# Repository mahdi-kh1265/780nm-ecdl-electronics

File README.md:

# 780nm-ecdl-electronics

Control, interface, piezo-actuation, and power electronics for POSM's 780 nm Littrow external-cavity diode laser.

This repository contains the custom electronics surrounding POSM's 780 nm ECDL used for rubidium spectroscopy, modulation-transfer spectroscopy (MTS), and laser-frequency stabilization.

The system is divided into three hardware projects:

1. **`ecdl-laser-bboard`** — laser/TEC controller interface, slow current bias, fast current modulation, monitoring, and Red Pitaya/FPGA connectivity.
2. **`780nm-ecdl-grating`** — high-voltage piezoelectric grating actuator driver for ECDL tuning, scanning, and slow lock correction.
3. **`780nm-grating-psu`** — dedicated low-voltage and high-voltage power supply for the grating driver. **Currently in development.**

---

# ECDL Hardware Context

The current system is designed around a 780 nm Littrow ECDL for the rubidium D2 region.

The broader laser assembly includes:

* 780 nm laser diode
* temperature-controlled TO-can mount
* diffraction grating in Littrow configuration
* piezoelectric grating actuator
* optical isolator
* free-space output optics
* fiber launch into the spectroscopy system
* MTS-based atomic frequency reference

The electronics in this repository do **not** contain the complete spectroscopy lock. MTS RF/demodulation electronics and FPGA lock logic are maintained separately.

---

# 1. `ecdl-laser-bboard`

## Laser / TEC Interface and Current-Control Baseboard

`ecdl-laser-bboard` is the central electrical interface between the laser assembly, commercial laser/TEC controller, Red Pitaya/FPGA control system, and monitoring hardware.

It is intentionally an **interface and control-conditioning board**, not a replacement precision laser-current driver.

The commercial LD/TEC controller remains responsible for the actual regulated laser current and TEC control.

# 2. `780nm-ecdl-grating`

## High-Voltage ECDL Grating / PZT Driver

The second major PCB drives the piezoelectric actuator mounted behind the Littrow grating.

Moving the piezo changes the diffraction-grating angle and external-cavity length, which changes the ECDL frequency.

The board is intended for:

* laser-frequency scanning
* finding rubidium spectroscopy features
* setting the PZT operating point
* lock acquisition
* slow frequency correction
* recentering the fast current actuator during long locks

---

# 3. `780nm-grating-psu`

## Dedicated Grating-Driver Power Supply

> **Current repository status: this PCB is still in development.**

The intended role of this board is to generate all rails required by `780nm-ecdl-grating` from a low-voltage system input.

Primary design goals include:

* low-noise analog rails
* controlled startup
* current limiting and fault protection
* sufficient +155 V power for dynamic piezo charging
* proper high-voltage spacing
* low coupling from the switching converters into the analog control circuitry

The committed KiCad project should be treated as a placeholder until the PSU design is frozen and reviewed.

# 4. Repository Structure

```text
780nm-ecdl-electronics/
│
├── ecdl-laser-bboard/
│   ├── ecdl-laser-bboard.kicad_sch
│   ├── sch2.kicad_sch
│   ├── sch3.kicad_sch
│   ├── ecdl-laser-bboard.kicad_pcb
│   ├── ecdl-laser-bboard.kicad_pro
│   └── libraries/
│
├── 780nm-ecdl-grating/
│   ├── 780nm-ecdl-grating.kicad_sch
│   ├── 780nm-ecdl-grating.kicad_pcb
│   ├── 780nm-ecdl-grating.kicad_pro
│   └── libraries/
│
├── 780nm-grating-psu/
│   ├── 780nm-grating-psu.kicad_sch
│   ├── 780nm-grating-psu.kicad_pcb
│   └── 780nm-grating-psu.kicad_pro
│
├── LICENSE
└── README.md
```

The current projects use **KiCad 10** format.

---

# 5. Major Components

| Function                      | Component                      | PCB                  |
| ----------------------------- | ------------------------------ | -------------------- |
| High-voltage PZT amplifier    | TI OPA462                      | `780nm-ecdl-grating` |
| Precision analog buffering    | TI OPA192                      | `780nm-ecdl-grating` |
| Precision reference           | ADR4550                        | `780nm-ecdl-grating` |
| Slow laser-current bias DAC   | TI DAC80501                    | `ecdl-laser-bboard`  |
| Precision analog conditioning | TI OPA4192                     | `ecdl-laser-bboard`  |
| True-zero negative supply     | TI LM7705                      | `ecdl-laser-bboard`  |
| Input protection / eFuse      | TPS25947 family                | `ecdl-laser-bboard`  |
| Low-noise power conversion    | LT862x family                  | `ecdl-laser-bboard`  |
| ECDL mount interface          | DB9 / DB15                     | `ecdl-laser-bboard`  |
| FPGA/control interface        | Red Pitaya header / analog I/O | `ecdl-laser-bboard`  |

Refer to the KiCad schematics rather than this table for current component values and installed options.

---

# 6. Recommended Bring-Up Sequence

The complete ECDL should **not** be the first load connected during PCB bring-up.

Each board should be tested independently first.

## `ecdl-laser-bboard`

1. Inspect for assembly faults and shorts.
2. Verify resistance from each power rail to ground.
3. Apply current-limited 12 V with the laser and TEC disconnected.
4. Verify eFuse behavior.
5. Verify all 5 V and logic rails.
6. Verify the LM7705 negative rail.
7. Verify DAC80501 communication over SPI.
8. Sweep the slow-bias DAC and measure `V_BIAS`.
9. Apply a known voltage to `RP_IN`.
10. Verify each fast-loop sensitivity setting.
11. Verify the complete summed `EXT_LD_SET` transfer function.
12. Verify `RP_EN` / `LD_SHD` behavior.
13. Inject known monitor voltages and verify each buffer.
14. Verify DB9/DB15 continuity pin-by-pin.
15. Connect the commercial LD/TEC controller without a laser.
16. Only after the interface is characterized should the real ECDL mount be connected.

## `780nm-ecdl-grating`

1. Bring up the low-voltage rails first.
2. Verify the precision reference.
3. Verify RP input buffering and filtering.
4. Verify the analog summer at low voltage.
5. Verify OPA462 enable/status behavior.
6. Apply the +155 V rail with a current limit and no piezo attached.
7. Command several static output voltages.
8. Verify `PIEZO_OUT` with a properly rated measurement setup.
9. Verify the monitor-divider calibration.
10. Test initially with a dummy capacitive load.
11. Apply triangle/ramp waveforms.
12. Verify stability, overshoot, heating, and slew behavior.
13. Connect the real grating piezo only after the electrical tests pass.

---

# 7. Characterization Data to Add

Once assembled, this repository should contain measured performance rather than only schematic intent.

Recommended measurements include:

## Laser baseboard

* 12 V input current
* rail noise
* DAC transfer function
* DAC INL/DNL where useful
* fast-input transfer function
* each fast sensitivity setting
* complete `EXT_LD_SET` transfer function
* monitor-channel gain and offset
* monitor noise
* shutdown latency
* temperature drift
* crosstalk between fast and slow controls

## Grating controller

* output voltage range
* command-to-PZT gain
* center-voltage adjustment range
* monitor-divider calibration
* output noise spectral density
* output ripple
* PZT step response
* triangle-wave fidelity
* capacitive-load stability
* maximum practical slew rate
* OPA462 temperature
* large-signal bandwidth

## Closed-loop ECDL

Eventually:

* PZT tuning coefficient in MHz/V
* current tuning coefficient in MHz/mA
* scan range
* mode-hop-free tuning range
* fast-loop bandwidth
* slow-loop/recenter behavior
* frequency-noise spectrum
* long-term lock stability
* actuator saturation statistics

A future structure could be:

```text
measurements/
├── laser-bboard/
│   ├── fast_path/
│   ├── slow_bias/
│   ├── monitors/
│   └── power/
│
├── grating/
│   ├── transfer_function/
│   ├── noise/
│   ├── pzt_response/
│   └── hv_monitor/
│
└── locked_ecdl/
    ├── tuning_coefficients/
    ├── spectra/
    ├── lock_performance/
    └── drift/
```

---

# 8. Safety

This repository contains circuits capable of damaging:

* laser diodes
* TECs
* piezoelectric actuators
* ADC/FPGA inputs
* test equipment
* and the operator if high-voltage nodes are handled improperly.

In particular:

### Laser diodes

Laser diodes can be destroyed by brief overcurrent, ESD, reverse voltage, connector mistakes, or uncontrolled startup transients.

### PZT driver

The grating board uses approximately **+155 V**.

Treat the high-voltage section as hazardous laboratory electronics even though available current is limited.

Do not probe `PIEZO_OUT` with equipment or accessories that are not appropriately voltage-rated.

### Connector pinouts

Always verify:

* DB9 pinout
* DB15 pinout
* laser polarity
* monitor-photodiode polarity
* TEC polarity
* thermistor connections
* controller common/reference

before connecting the actual laser mount.

---

# License

Released under the license included in [`LICENSE`](LICENSE).

---

## POSM

**Photonics and Optical Sciences Club at Minnesota**
University of Minnesota

[POSM website](https://posmphotonics.org/)

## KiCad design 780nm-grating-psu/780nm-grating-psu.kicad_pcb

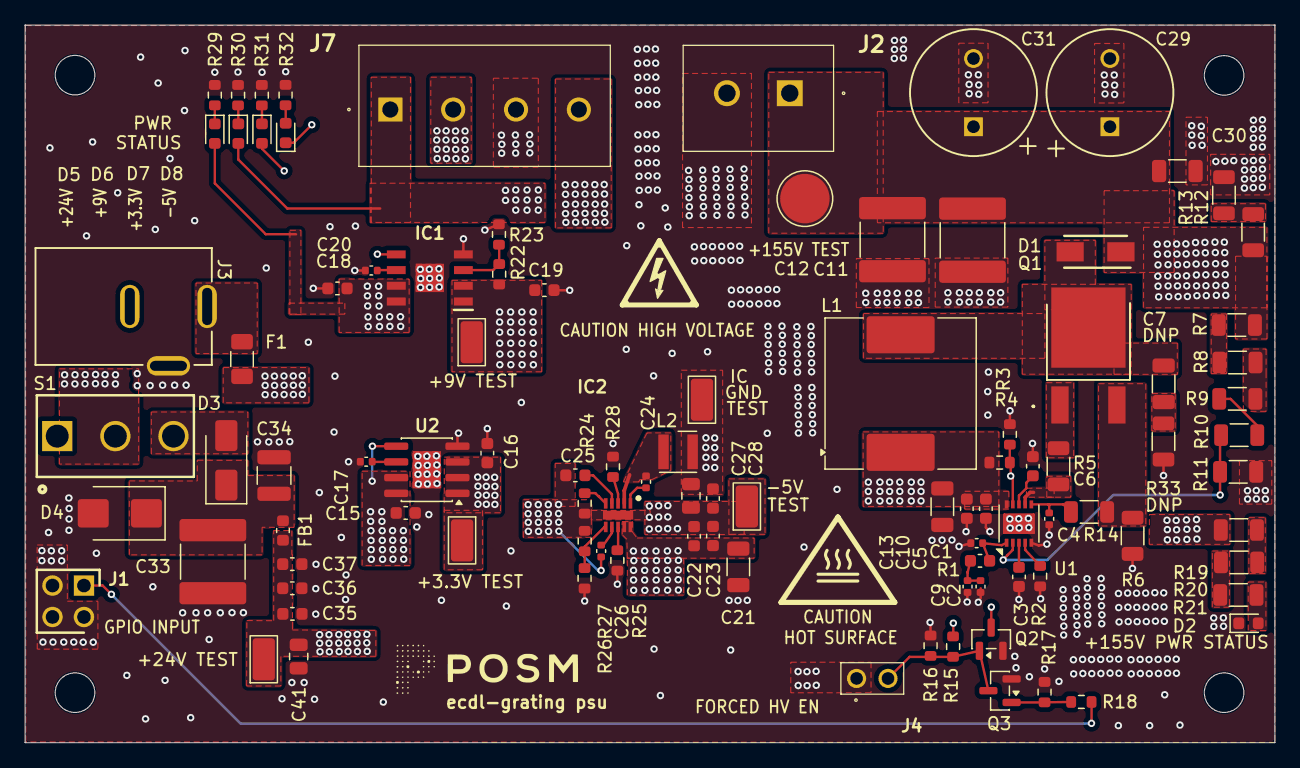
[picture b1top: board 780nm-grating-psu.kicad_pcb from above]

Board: 4 copper layers, 101.0 x 58.0 mm, 100 parts (0 on the bottom side), 47 nets.

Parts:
+3.3V TEST: +3.3V; TestPoint_Keystone_5015_Micro_Mini
+9V TEST: +9V TEST; TestPoint_Keystone_5015_Micro_Mini
+24V TEST: +24V; TestPoint_Keystone_5015_Micro_Mini
+155V TEST: +155V; TestPoint_Pad_D4.0mm
-5V: -5V; TestPoint_Keystone_5015_Micro_Mini
C1: 100p; C_0402_1005Metric
C2: 22n; C_0402_1005Metric
C3, C10, C22, C25, C35: 1u; C_0603_1608Metric
C4, C9: DNP; C_0402_1005Metric
C5, C23, C36: 0.1u; C_0603_1608Metric
C6, C15, C16, C18, C19, C28: 4.7u; C_0603_1608Metric
C7: DNP; C_1206_3216Metric
C11, C12: 2.2u; C_2220_5750Metric
C13, C21: 22u; C_1206_3216Metric
C17, C20, C26: 10n; C_0402_1005Metric
C24: 47n; C_0402_1005Metric
C27: 10u; C_0805_2012Metric
C29, C31: 22u; PCAP_10x20-THRU-ELECT_NCA
C30: 0.1u; C_1206_3216Metric
C33: 47u; C_2220_5750Metric
C34: 10u; C_1210_3225Metric
C37: 10n; C_0603_1608Metric
C41: 4.7u; C_0805_2012Metric
D1: STTH1R04A; DIOM5126X265N
D2: HV STATUS; LED_0603_1608Metric
D3: ​​​STPS2H100A; D_SMA
D4: SMBJ24CA-TR; D_SMB
D5, D6, D7, D8: LED; LED_0603_1608Metric
F1: 0437001.WRA; Fuse_1206_3216Metric
FB1: 1000 ohms; L_0603_1608Metric
IC1: ADP7142ARDZ-5.0-R7; SOIC127P600X175-9N
IC2: LT8618EDDB#TRPBF; SON50P200X300X80-11N-D
IC : GND; TestPoint_Keystone_5015_Micro_Mini
J1: TSW-102-07-G-D; HDRV4W64P254_2X2_508X508X838P
J2: 1755736
J3: 54-00166; CONN3_54-00166_TEN
J4: TSW-102-07-G-S; TSW-102-XX-YY-S
J7: 1715747
L1: 1.5m; L_Coilcraft_MSS1210H-XXX
L2: 33u; L_Wurth_WE-LQSH-3012
Q1: FDD3N40TM
Q2, Q3: 2N7002; SOT-23
R1: 47k; C_0603_1608Metric
R2: 41.2k; R_0603_1608Metric
R3: 34.8k; R_0603_1608Metric
R4: 511k; R_0603_1608Metric
R5, R14: 0; R_1206_3216Metric
R6: 0.3; R_1206_3216Metric
R7, R8, R9: 511k; R_1206_3216Metric
R10: 20k; R_1206_3216Metric
R11: 16.2k; R_1206_3216Metric
R12, R13: 220k; R_1206_3216Metric
R15: 390k; R_0603_1608Metric
R16, R17: 100k; R_0603_1608Metric
R18, R29: 10k; R_0603_1608Metric
R19, R20, R21: 120k; R_1206_3216Metric
R22: 39.9k; R_0603_1608Metric
R23, R25: 49.9k; R_0603_1608Metric
R24: 18.2k; R_0603_1608Metric
R26: 1.02M; R_0603_1608Metric
R27: 187k; R_0603_1608Metric
R28: 0; R_0603_1608Metric
R30: 3.3k; R_0603_1608Metric
R31: 1k; R_0603_1608Metric
R32: 2.2k; R_0603_1608Metric
R33: DNP; R_1206_3216Metric
S1: 1101M2S3CQE2; SW_1101M2S3CQE2
SYM: Caution_Hot_Surface_FinalFit_12x12mm_Silk
U1: LT3757AEDD; DFN-10-1EP_3x3mm_P0.5mm_EP1.55x2.48mm
U2: ADP7142ARDZ-3.3; SOIC-8-1EP_3.9x4.9mm_P1.27mm_EP2.29x3mm

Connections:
+3.3V: +3.3V TEST.1 (1_1), C16.2, D7.2 (A), J7.2, U2.1 (VOUT), U2.2 (VOUT), U2.3 (SENSE/ADJ)
+9V: +9V TEST.1 (1_1), C19.2, D6.2 (A), IC1.1 (VOUT_1), IC1.2 (VOUT_2), J7.1, R22.1
+24V: +24V TEST.1 (1_1), C5.1, C10.1, C13.1, C15.2, C18.2, C21.1, C22.1, C23.1, C35.1, C36.1, C37.1, C41.1, D5.2 (A), FB1.2, IC1.5 (EN), IC1.7 (VIN_1), IC1.8 (VIN_2), IC2.9 (EN/UV), IC2.10 (VIN), L1.1, R4.2, R15.2, U1.10 (VIN), U2.5 (EN), U2.7 (VIN), U2.8 (VIN)
+24V_RAW1: F1.2, S1.2
+24V_RAW2: D3.2 (A), S1.3
+155V: +155V TEST.1 (1_1), C11.2, C12.2, C29.1, C30.1, C31.1, D1.1 (K), J2.1, R7.1, R12.1, R19.1
-5V: -5V.1 (1_1), C22.2, C23.2, C25.2, C26.1, C27.1, C28.1, D8.1 (K), IC2.11 (GND), J7.4, R24.2, R27.2
FB: IC2.6 (FB), R26.2, R27.1
FBX_+155V: R10.2, R11.1, U1.2 (FBX)
G: Q1.1 (G), R5.2
GND: C1.2, C2.2, C3.2, C4.2, C5.2, C6.1, C9.2, C10.2, C11.1, C12.1, C13.2, C15.1, C16.1, C17.1, C18.1, C19.1, C20.1, C21.2, C27.2, C28.2, C29.2, C30.2, C31.2, C33.2, C34.2, C35.2, C36.2, C37.2, C41.2, D2.1 (K), D4.2 (A), IC1.4 (GND_1), IC1.9 (GND_2), IC.1 (1_1), J1.2, J1.3, J1.4, J2.2, J4.1, J7.3, L2.2, Q2.2 (S), Q3.2 (S), R2.1, R3.1, R6.1, R11.2, R13.2, R16.1, R17.1, R23.2, R25.2, R26.1, R28.1, R29.1, R30.1, R31.1, R32.1, R33.2, U1.5 (SYNC), U1.11 (GND), U2.4 (GND), U2.9 (GND)
HV_EN: J1.1, R18.1
unnamed: C2.1, C9.1, R1.2
unnamed: C7.2, R33.1
unnamed: C7.1, D1.2 (A), L1.2, Q1.2 (S)
unnamed: D2.2 (A), R21.2
unnamed: C33.1, C34.1, D3.1 (K), D4.1 (K), FB1.1
unnamed: D5.1 (K), R29.2
unnamed: D6.1 (K), R30.2
unnamed: D7.1 (K), R31.2
unnamed: D8.2 (A), R32.2
unnamed: IC1.3 (SENSE/ADJ), R22.2, R23.1
unnamed: C20.2, IC1.6 (SS)
unnamed: IC2.3 (BIAS), R28.2
unnamed: C24.1, IC2.1 (BST)
unnamed: C25.1, IC2.4 (INTVCC)
unnamed: IC2.5 (RT), R24.1
unnamed: C24.2, IC2.2 (SW), L2.1
unnamed: C26.2, IC2.7 (TR/SS)
unnamed: Q1.3 (D), R6.2, R14.1
unnamed: J4.2, Q2.1 (G), Q3.3 (D), R15.1, R16.2
unnamed: Q3.1 (G), R17.2, R18.2
unnamed: R7.2, R8.1
unnamed: R8.2, R9.1
unnamed: R9.2, R10.1
unnamed: R12.2, R13.1
unnamed: R19.2, R20.1
unnamed: R20.2, R21.1
unnamed: R5.1, U1.7 (GATE)
unnamed: C6.2, U1.8 (INTVCC)
unnamed: R2.2, U1.4 (RT)
unnamed: C4.1, R14.2, U1.6 (SENSE)
unnamed: C3.1, U1.3 (SS)
unnamed: C1.1, R1.1, U1.1 (VC)
unnamed: C17.2, U2.6 (SS)
PG: IC2.8 (PG), R25.1
SHDN: Q2.3 (D), R3.2, R4.1, U1.9 (~SHDN/UVLO)

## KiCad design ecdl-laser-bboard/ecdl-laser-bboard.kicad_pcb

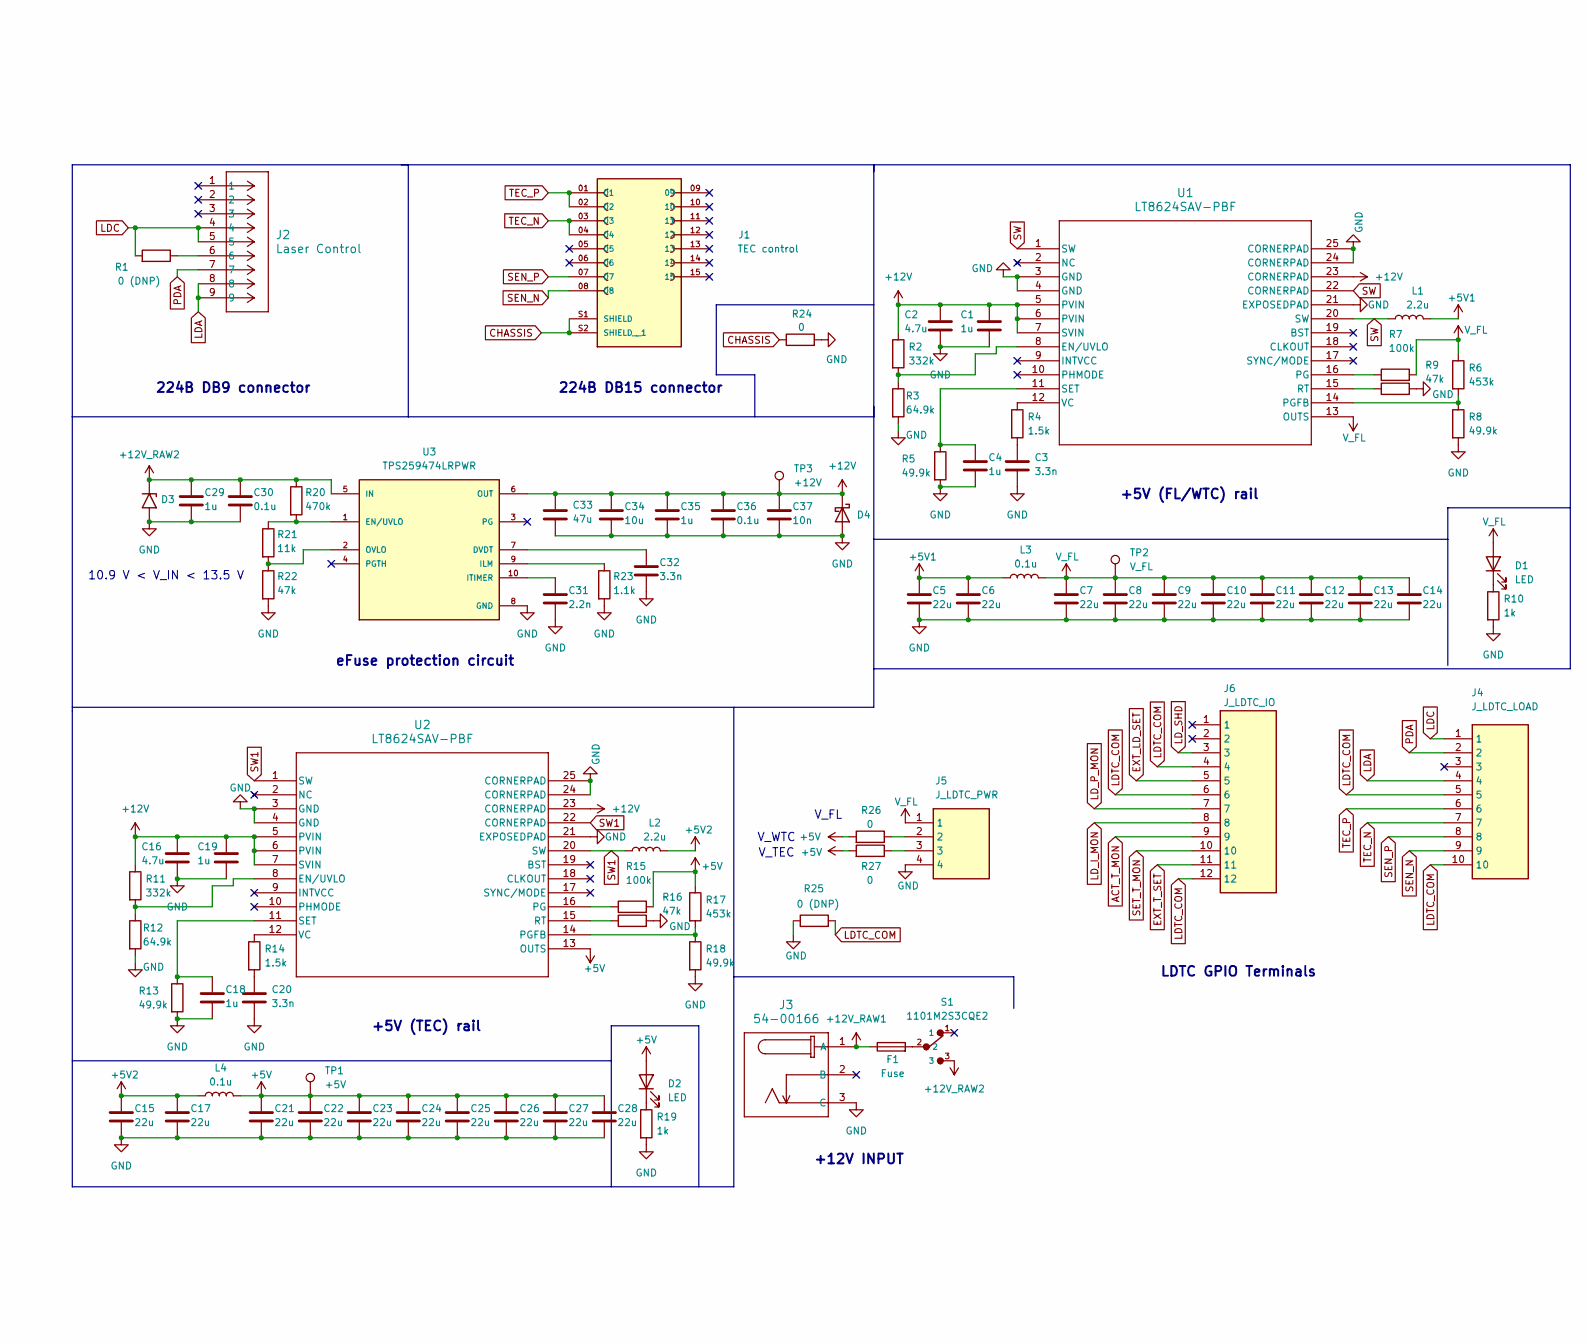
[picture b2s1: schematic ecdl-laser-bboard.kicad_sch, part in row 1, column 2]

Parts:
C1, C4, C18, C19, C29, C35: 1u; C_0603_1608Metric
C2, C16: 4.7u; C_0603_1608Metric
C3, C20, C32: 3.3n; C_0603_1608Metric
C5, C7, C8, C9, C10, C11, C12, C13, C14, C15, C17, C21, C22, C23, C24, C25, C26, C27, C28: 22u; C_1210_3225Metric
C6: 22u; C_0603_1608Metric
C30, C36: 0.1u; C_0603_1608Metric
C31: 2.2n; C_0603_1608Metric
C33: 47u; C_1210_3225Metric
C34: 10u; C_0603_1608Metric
C37: 10n; C_0603_1608Metric
D1, D2: LED; LED_0603_1608Metric
D3: D_SMB
D4: B330A-13-F; D_SMA
F1: Fuse; FUSC6127X294N
J1: TEC control; AMPHENOL_D15S33E4GV00LF; PARTREV D
J2: Laser Control; CONN_D09S33E4GV00LF_AMP
J3: 54-00166; CONN3_54-00166_TEN
J4: J_LDTC_LOAD; 1757323; Mouser Part Number 651-1757323
J5: J_LDTC_PWR; 1757268; Mouser Part Number 651-1757268
J6: J_LDTC_IO; 1803374; Mouser Part Number 651-1803374
L1, L2: 2.2u; XEL6030222MEC
L3, L4: 0.1u; XEL6030222MEC
R1, R25: 0 (DNP); R_0805_2012Metric
R2, R11: 332k; R_0603_1608Metric
R3, R12: 64.9k; R_0603_1608Metric
R4, R14: 1.5k; R_0603_1608Metric
R5, R8, R13, R18: 49.9k; R_0603_1608Metric
R6, R17: 453k; R_0603_1608Metric
R7, R15: 100k; R_0603_1608Metric
R9, R16, R22: 47k; R_0603_1608Metric
R10, R19: 1k; R_0805_2012Metric
R20: 470k; R_0603_1608Metric
R21: 11k; R_0603_1608Metric
R23: 1.1k; R_0603_1608Metric
R24, R26, R27: 0; R_0805_2012Metric
S1: 1101M2S3CQE2; SW_1101M2S3CQE2
TP1: +5V; TestPoint_Keystone_5015_Micro_Mini
TP2: V_FL; TestPoint_Keystone_5015_Micro_Mini
TP3: +12V; TestPoint_Keystone_5015_Micro_Mini
U1, U2: LT8624SAV-PBF; 05-08-1602_Rev_A_ADI
U3: TPS259474LRPWR; IC_TPS259474ARPWR; PARTREV A

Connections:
+5V: C21.1, C22.1, C23.1, C24.1, C25.1, C26.1, C27.1, C28.1, D2.2 (A), L4.2, R15.2, R17.1, R26.2, R27.2, TP1.1, U2.13 (OUTS); also elsewhere on the board
+5V1: C5.1, C6.1, L1.2, L3.1
+5V2: C15.1, C17.1, L2.2, L4.1
+12V: C1.1, C2.1, C16.1, C19.1, C33.1, C34.1, C35.1, C36.1, C37.1, D4.1 (K), R2.1, R11.1, TP3.1, U1.5 (PVIN), U1.6 (PVIN), U1.7 (SVIN), U1.23 (CORNERPAD), U2.5 (PVIN), U2.6 (PVIN), U2.7 (SVIN), U2.23 (CORNERPAD), U3.6 (OUT); also elsewhere on the board
+12V_RAW1: F1.1, J3.1 (A), J3.A
+12V_RAW2: C29.1, C30.1, D3.1 (A1), R20.1, S1.3, U3.5 (IN)
CHASSIS: J1.S1 (SHIELD), J1.S2 (SHIELD__1), J2.10, J2.11, R24.1
LDA: J2.8, J2.9, J4.4
LDC: J2.4, J2.5, J4.1, R1.2
unnamed: C3.1, R4.2
unnamed: C20.1, R14.2
unnamed: D1.1 (K), R10.1
unnamed: D2.1 (K), R19.1
unnamed: F1.2, S1.2
unnamed: J2.6, R1.1
unnamed: J5.2, R26.1
unnamed: J5.3, R27.1
unnamed: R2.2, R3.1, U1.8 (EN/UVLO)
unnamed: R7.1, U1.16 (PG)
unnamed: R6.2, R8.1, U1.14 (PGFB)
unnamed: R9.1, U1.15 (RT)
unnamed: C4.1, R5.1, U1.11 (SET)
unnamed: R4.1, U1.12 (VC)
unnamed: R11.2, R12.1, U2.8 (EN/UVLO)
unnamed: R15.1, U2.16 (PG)
unnamed: R17.2, R18.1, U2.14 (PGFB)
unnamed: R16.1, U2.15 (RT)
unnamed: C18.1, R13.1, U2.11 (SET)
unnamed: R14.1, U2.12 (VC)
unnamed: C32.1, U3.7 (DVDT)
unnamed: R20.2, R21.1, U3.1 (EN/UVLO)
unnamed: R23.1, U3.9 (ILM)
unnamed: C31.1, U3.10 (ITIMER)
unnamed: R21.2, R22.1, U3.2 (OVLO)
PDA: J2.7, J4.2
SEN_N: J1.08, J4.9
SEN_P: J1.07, J4.8
SW: L1.1, U1.1 (SW), U1.20 (SW), U1.22 (CORNERPAD)
SW1: L2.1, U2.1 (SW), U2.20 (SW), U2.22 (CORNERPAD)
TEC_N: J1.03, J1.04, J4.7
TEC_P: J1.01, J1.02, J4.6
V_FL: C7.1, C8.1, C9.1, C10.1, C11.1, C12.1, C13.1, C14.1, D1.2 (A), J5.1, L3.2, R6.1, R7.2, TP2.1, U1.13 (OUTS); also elsewhere on the board

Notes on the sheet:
+12V INPUT
10.9 V < V_IN < 13.5 V
V_FL
224B DB15 connector
eFuse protection circuit
V_TEC
LDTC GPIO Terminals
+5V (FL/WTC) rail
+5V (TEC) rail
V_WTC
224B DB9 connector

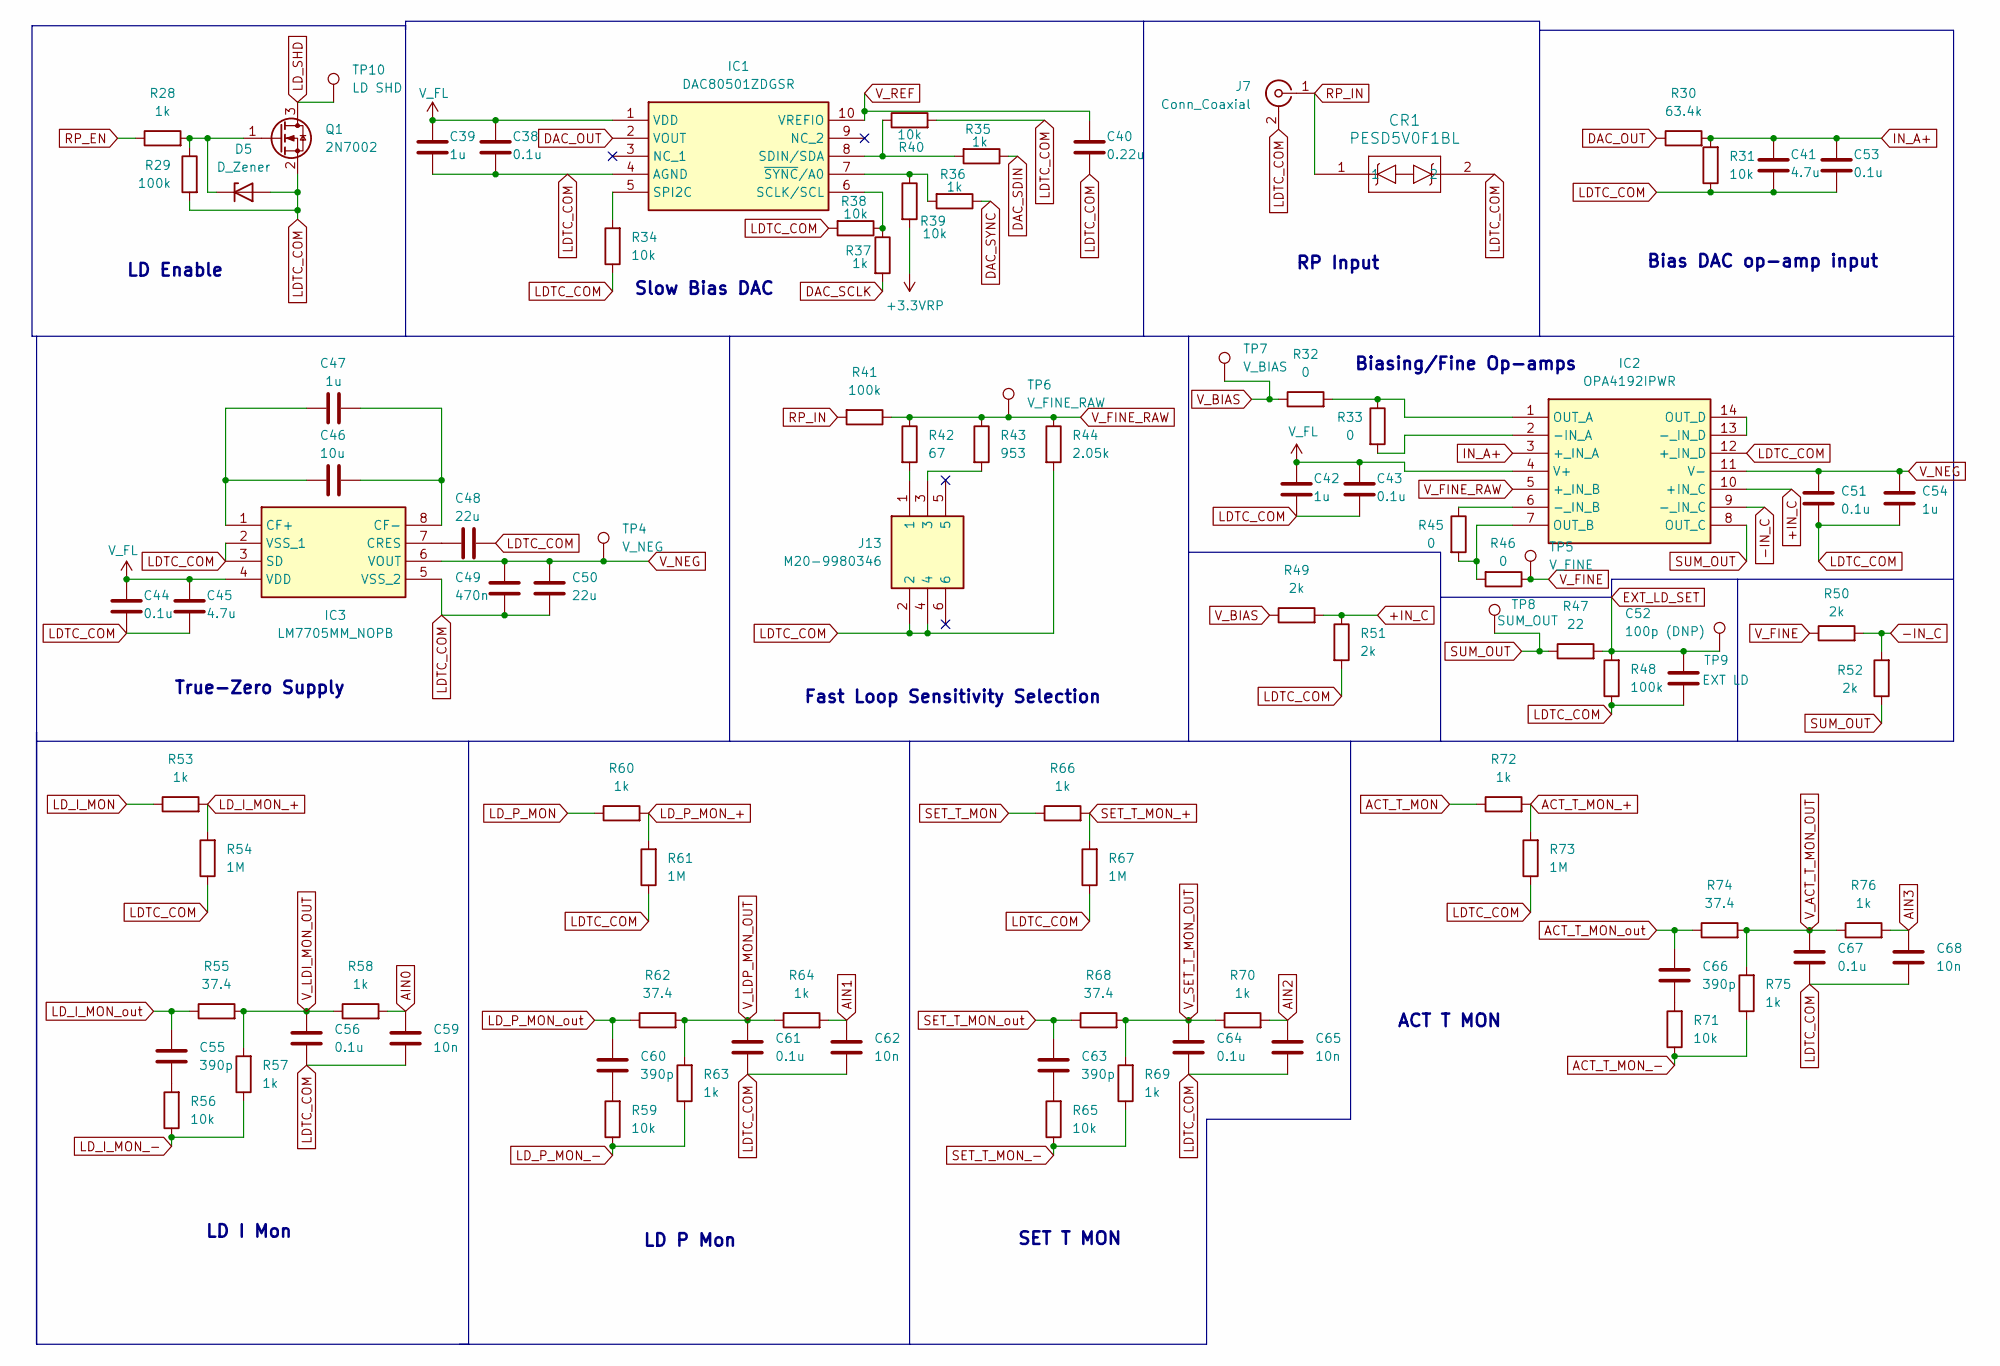
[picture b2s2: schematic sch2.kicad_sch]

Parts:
C38, C43, C44, C51, C53, C56, C61, C64, C67: 0.1u; C_0603_1608Metric
C39, C42, C47, C54: 1u; C_0603_1608Metric
C40: 0.22u; C_0603_1608Metric
C41, C45: 4.7u; C_0603_1608Metric
C46: 10u; C_0603_1608Metric
C48: 22u; C_0603_1608Metric
C49: 470n; C_0603_1608Metric
C50: 22u; C_1210_3225Metric
C52: 100p (DNP); C_0603_1608Metric
C55, C60, C63, C66: 390p; C_0402_1005Metric
C59, C62, C65, C68: 10n; C_0402_1005Metric
CR1: PESD5V0F1BL; DFN1006-2_SOD882_NEX
D5: D_Zener; D_SOD-323F
IC1: DAC80501ZDGSR; SOP50P490X110-10N; Mouser Part Number 595-DAC80501ZDGSR
IC2: OPA4192IPWR; SOP65P640X120-14N; Mouser Part Number 595-OPA4192IPWR
IC3: LM7705MM_NOPB; SOP65P490X110-8N; Mouser Part Number 926-LM7705MM/NOPB
J7: Conn_Coaxial; CONN_SMA-J-P-H-ST-TH1_SAI
J13: M20-9980346; HDRV6W64P254_2X3_762X508X864P; Mouser Part Number 855-M20-9980346
Q1: 2N7002; SOT-23
R28, R35, R36, R37, R53, R57, R58, R60, R63, R64, R66, R69, R70, R72, R75, R76: 1k; R_0603_1608Metric
R29, R41, R48: 100k; R_0603_1608Metric
R30: 63.4k; R_0603_1608Metric
R31, R34, R38, R39, R40, R56, R59, R65, R71: 10k; R_0603_1608Metric
R32, R33, R45, R46: 0; R_0805_2012Metric
R42: 67; R_0603_1608Metric
R43: 953; R_0603_1608Metric
R44: 2.05k; R_0603_1608Metric
R47: 22; R_0603_1608Metric
R49, R50, R51, R52: 2k; R_0603_1608Metric
R54, R61, R67, R73: 1M; R_0603_1608Metric
R55, R62, R68, R74: 37.4; R_0603_1608Metric
TP4: V_NEG; TestPoint_Keystone_5015_Micro_Mini
TP5: V_FINE; TestPoint_Keystone_5015_Micro_Mini
TP6: V_FINE_RAW; TestPoint_Keystone_5015_Micro_Mini
TP7: V_BIAS; TestPoint_Keystone_5015_Micro_Mini
TP8: SUM_OUT; TestPoint_Keystone_5015_Micro_Mini
TP9: EXT LD; TestPoint_Keystone_5015_Micro_Mini
TP10: LD SHD; TestPoint_Keystone_5015_Micro_Mini

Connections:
+3.3VRP: R39.2; also elsewhere on the board
+IN_C: IC2.10 (+IN_C), R49.2, R51.1
-IN_C: IC2.9 (-_IN_C), R50.2, R52.2
ACT_T_MON: R72.1; also elsewhere on the board
ACT_T_MON_+: R72.2, R73.2; also elsewhere on the board
ACT_T_MON_-: R71.1, R75.1; also elsewhere on the board
ACT_T_MON_out: C66.1, R74.1; also elsewhere on the board
AIN0: C59.1, R58.2; also elsewhere on the board
AIN1: C62.1, R64.2; also elsewhere on the board
AIN2: C65.1, R70.2; also elsewhere on the board
AIN3: C68.1, R76.2; also elsewhere on the board
DAC_OUT: IC1.2 (VOUT), R30.1
DAC_SCLK: R37.2; also elsewhere on the board
DAC_SDIN: R35.1; also elsewhere on the board
DAC_SYNC: R36.1; also elsewhere on the board
EXT_LD_SET: C52.1, R47.2, R48.2, TP9.1; also elsewhere on the board
IN_A+: C41.1, C53.1, IC2.3 (+_IN_A), R30.2, R31.2
LD_I_MON: R53.1; also elsewhere on the board
LD_I_MON_+: R53.2, R54.2; also elsewhere on the board
LD_I_MON_-: R56.1, R57.1; also elsewhere on the board
LD_I_MON_out: C55.1, R55.1; also elsewhere on the board
LD_P_MON: R60.1; also elsewhere on the board
LD_P_MON_+: R60.2, R61.2; also elsewhere on the board
LD_P_MON_-: R59.1, R63.1; also elsewhere on the board
LD_P_MON_out: C60.1, R62.1; also elsewhere on the board
LD_SHD: Q1.3 (D), TP10.1; also elsewhere on the board
unnamed: C55.2, R56.2
unnamed: C60.2, R59.2
unnamed: C63.2, R65.2
unnamed: C66.2, R71.2
unnamed: D5.1 (K), Q1.1 (G), R28.2, R29.1
unnamed: IC1.6 (SCLK/SCL), R37.1, R38.1
unnamed: IC1.8 (SDIN/SDA), R35.2, R40.1
unnamed: IC1.5 (SPI2C), R34.2
unnamed: IC1.7 (~SYNC/A0), R36.2, R39.1
unnamed: IC2.2 (-IN_A), R33.2
unnamed: IC2.6 (-_IN_B), R45.1
unnamed: IC2.13 (-_IN_D), IC2.14 (OUT_D)
unnamed: IC2.1 (OUT_A), R32.2, R33.1
unnamed: IC2.7 (OUT_B), R45.2, R46.2
unnamed: C46.1, C47.1, IC3.1 (CF+)
unnamed: C46.2, C47.2, IC3.8 (CF-)
unnamed: C48.1, IC3.7 (CRES)
unnamed: J13.1, R42.2
unnamed: J13.3, R43.2
RP_EN: R28.1; also elsewhere on the board
RP_IN: CR1.1, J7.1 (In), R41.2
SET_T_MON: R66.1; also elsewhere on the board
SET_T_MON_+: R66.2, R67.2; also elsewhere on the board
SET_T_MON_-: R65.1, R69.1; also elsewhere on the board
SET_T_MON_out: C63.1, R68.1; also elsewhere on the board
SUM_OUT: IC2.8 (OUT_C), R47.1, R52.1, TP8.1; also elsewhere on the board
V_ACT_T_MON_OUT: C67.1, R74.2, R75.2, R76.1; also elsewhere on the board
V_BIAS: R32.1, R49.1, TP7.1; also elsewhere on the board
V_FINE: R46.1, R50.1, TP5.1; also elsewhere on the board
V_FINE_RAW: IC2.5 (+_IN_B), R41.1, R42.1, R43.1, R44.1, TP6.1; also elsewhere on the board
V_FL: C38.1, C39.1, C42.1, C43.1, C44.1, C45.1, IC1.1 (VDD), IC2.4 (V+), IC3.4 (VDD); also elsewhere on the board
V_LDI_MON_OUT: C56.1, R55.2, R57.2, R58.1; also elsewhere on the board
V_LDP_MON_OUT: C61.1, R62.2, R63.2, R64.1; also elsewhere on the board
V_NEG: C49.2, C50.1, C51.1, C54.1, IC2.11 (V-), IC3.6 (VOUT), TP4.1 (1_1); also elsewhere on the board
V_REF: C40.1, IC1.10 (VREFIO)
V_SET_T_MON_OUT: C64.1, R68.2, R69.2, R70.1; also elsewhere on the board

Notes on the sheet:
ACT T MON
SET T MON
LD P Mon
Fast Loop Sensitivity Selection
RP Input
LD Enable
Slow Bias DAC
LD I Mon
True-Zero Supply
Bias DAC op-amp input
Biasing/Fine Op-amps

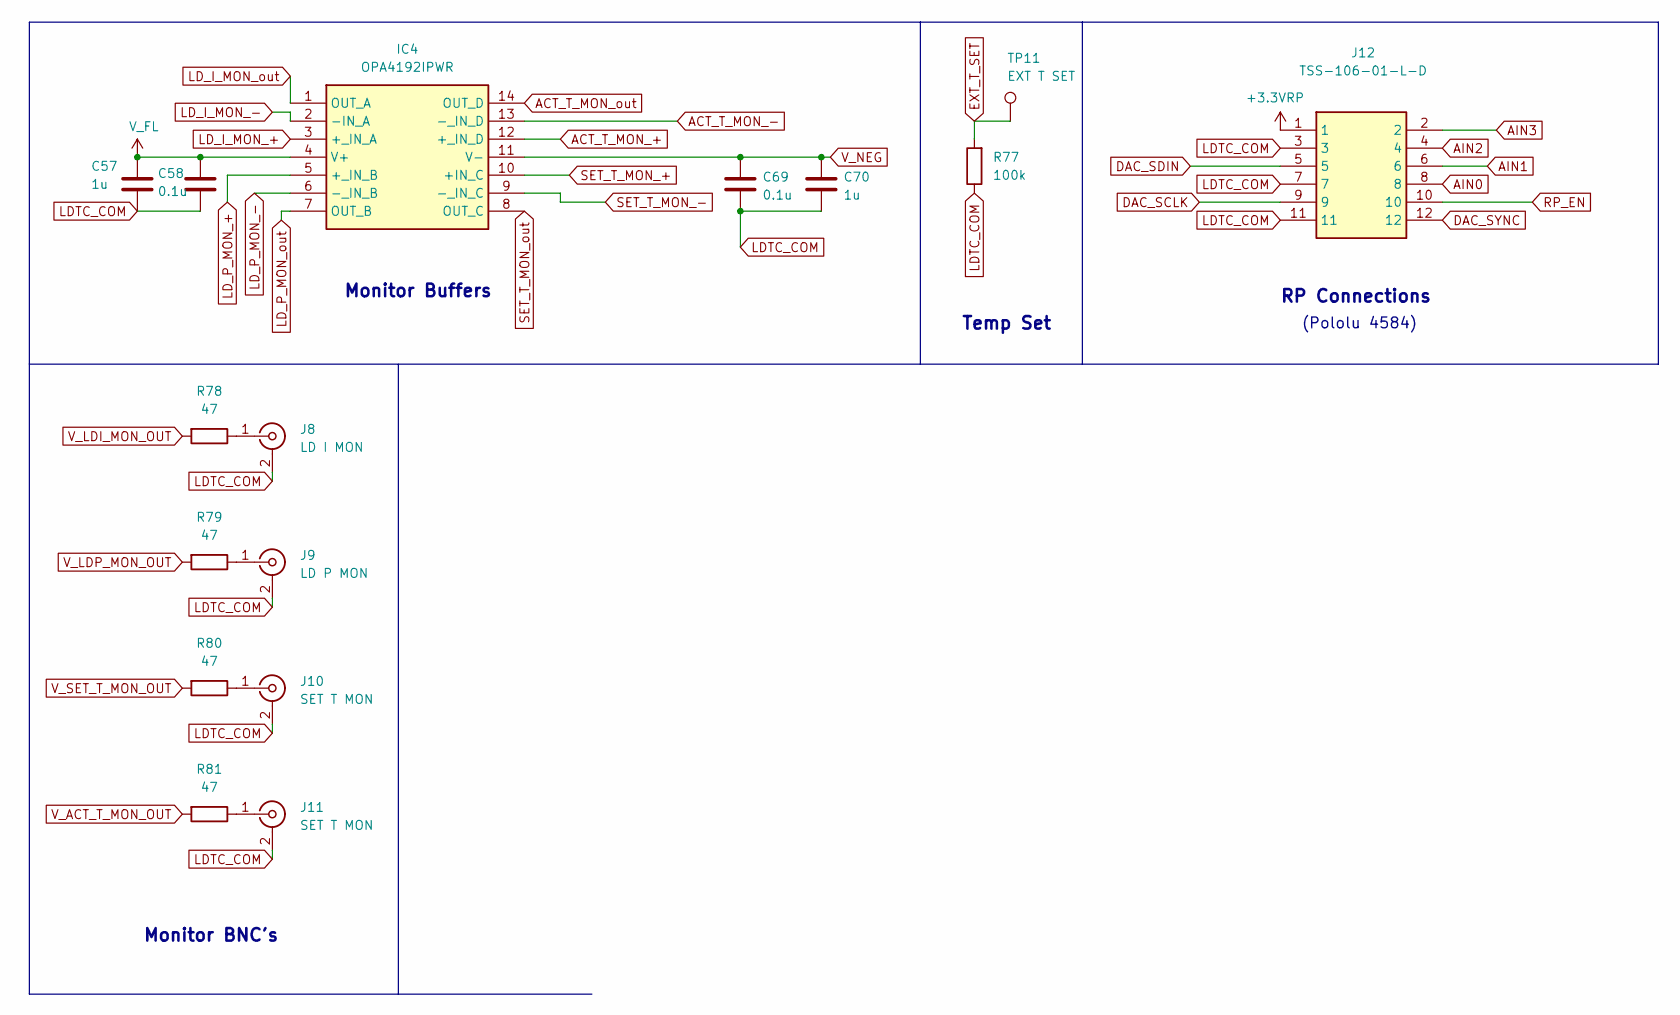
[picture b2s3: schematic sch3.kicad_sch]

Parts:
C57, C70: 1u; C_0603_1608Metric
C58, C69: 0.1u; C_0603_1608Metric
IC4: OPA4192IPWR; SOP65P640X120-14N; Mouser Part Number 595-OPA4192IPWR
J8: LD I MON; CONN_112404_AMP
J9: LD P MON; CONN_112404_AMP
J10, J11: SET T MON; CONN_112404_AMP
J12: TSS-106-01-L-D; TSS-106-XX-YYY-D; Mouser Part Number 200-TSS10601LD
R77: 100k; R_0603_1608Metric
R78, R79, R80, R81: 47; R_0603_1608Metric
TP11: EXT T SET; TestPoint_Keystone_5015_Micro_Mini

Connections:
+3.3VRP: J12.1; also elsewhere on the board
ACT_T_MON_+: IC4.12 (+_IN_D); also elsewhere on the board
ACT_T_MON_-: IC4.13 (-_IN_D); also elsewhere on the board
ACT_T_MON_out: IC4.14 (OUT_D); also elsewhere on the board
AIN0: J12.8; also elsewhere on the board
AIN1: J12.6; also elsewhere on the board
AIN2: J12.4; also elsewhere on the board
AIN3: J12.2; also elsewhere on the board
DAC_SCLK: J12.9; also elsewhere on the board
DAC_SDIN: J12.5; also elsewhere on the board
DAC_SYNC: J12.12; also elsewhere on the board
EXT_T_SET: R77.2, TP11.1; also elsewhere on the board
LD_I_MON_+: IC4.3 (+_IN_A); also elsewhere on the board
LD_I_MON_-: IC4.2 (-IN_A); also elsewhere on the board
LD_I_MON_out: IC4.1 (OUT_A); also elsewhere on the board
LD_P_MON_+: IC4.5 (+_IN_B); also elsewhere on the board
LD_P_MON_-: IC4.6 (-_IN_B); also elsewhere on the board
LD_P_MON_out: IC4.7 (OUT_B); also elsewhere on the board
unnamed: J8.1 (In), R78.1
unnamed: J9.1 (In), R79.1
unnamed: J10.1 (In), R80.1
unnamed: J11.1 (In), R81.1
RP_EN: J12.10; also elsewhere on the board
SET_T_MON_+: IC4.10 (+IN_C); also elsewhere on the board
SET_T_MON_-: IC4.9 (-_IN_C); also elsewhere on the board
SET_T_MON_out: IC4.8 (OUT_C); also elsewhere on the board
V_ACT_T_MON_OUT: R81.2; also elsewhere on the board
V_FL: C57.1, C58.1, IC4.4 (V+); also elsewhere on the board
V_LDI_MON_OUT: R78.2; also elsewhere on the board
V_LDP_MON_OUT: R79.2; also elsewhere on the board
V_NEG: C69.1, C70.1, IC4.11 (V-); also elsewhere on the board
V_SET_T_MON_OUT: R80.2; also elsewhere on the board

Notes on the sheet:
RP Connections
Temp Set
Monitor Buffers
(Pololu 4584)
Monitor BNC's

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
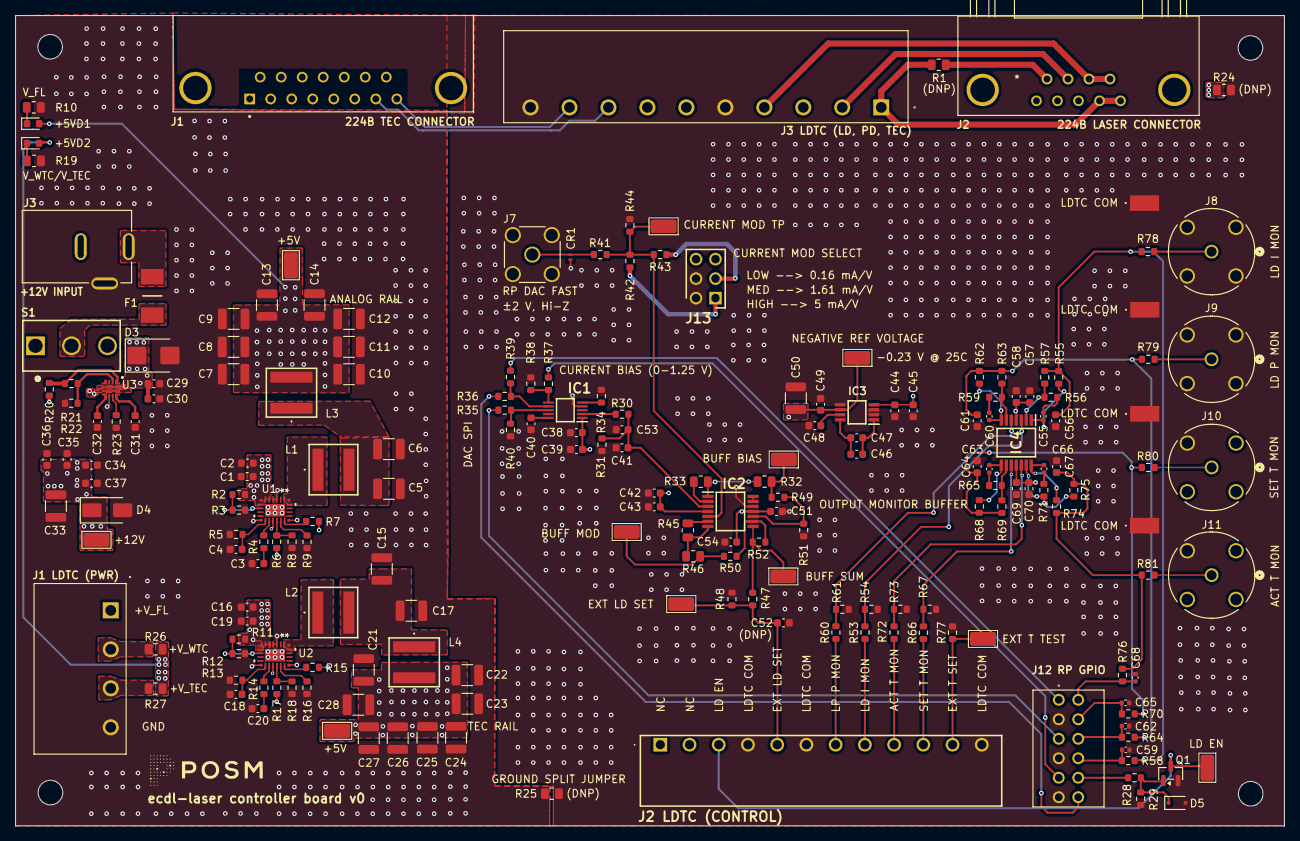
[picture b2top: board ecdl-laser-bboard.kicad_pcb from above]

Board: 4 copper layers, 165.4 x 105.7 mm, 199 parts (0 on the bottom side), 110 nets.

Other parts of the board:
+5V: V_FL; TestPoint_Keystone_5015_Micro_Mini
+5V#2: +5V; TestPoint_Keystone_5015_Micro_Mini
+12V: +12V; TestPoint_Keystone_5015_Micro_Mini
BUFF BIAS: V_BIAS; TestPoint_Keystone_5015_Micro_Mini
BUFF MOD: V_FINE; TestPoint_Keystone_5015_Micro_Mini
BUFF SUM: SUM_OUT; TestPoint_Keystone_5015_Micro_Mini
C52 : 100p (DNP); C_0603_1608Metric
CURRENT MOD TP: V_FINE_RAW; TestPoint_Keystone_5015_Micro_Mini
EXT LD SET: EXT LD; TestPoint_Keystone_5015_Micro_Mini
EXT T TEST: EXT T SET; TestPoint_Keystone_5015_Micro_Mini
J2 LDTC (CONTROL): J_LDTC_IO; 1803374
LD EN: LD SHD; TestPoint_Keystone_5015_Micro_Mini
LDTC COM: 5019
LDTC COM#2, LDTC COM#3, LDTC COM#4: 5019

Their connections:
+5V: +5V#2.1 (1_1); also elsewhere on the board
+12V: +12V.1 (1_1); also elsewhere on the board
ACT_T_MON: J2 LDTC (CONTROL).9; also elsewhere on the board
EXT_LD_SET: C52.1, EXT LD SET.1 (1_1), J2 LDTC (CONTROL).5; also elsewhere on the board
EXT_T_SET: EXT T TEST.1 (1_1), J2 LDTC (CONTROL).11; also elsewhere on the board
LD_I_MON: J2 LDTC (CONTROL).8; also elsewhere on the board
LD_P_MON: J2 LDTC (CONTROL).7; also elsewhere on the board
LD_SHD: J2 LDTC (CONTROL).3, LD EN.1 (1_1); also elsewhere on the board
SET_T_MON: J2 LDTC (CONTROL).10; also elsewhere on the board
SUM_OUT: BUFF SUM.1 (1_1); also elsewhere on the board
V_BIAS: BUFF BIAS.1 (1_1); also elsewhere on the board
V_FINE: BUFF MOD.1 (1_1); also elsewhere on the board
V_FINE_RAW: CURRENT MOD TP.1 (1_1); also elsewhere on the board
V_FL: +5V.1 (1_1); also elsewhere on the board
